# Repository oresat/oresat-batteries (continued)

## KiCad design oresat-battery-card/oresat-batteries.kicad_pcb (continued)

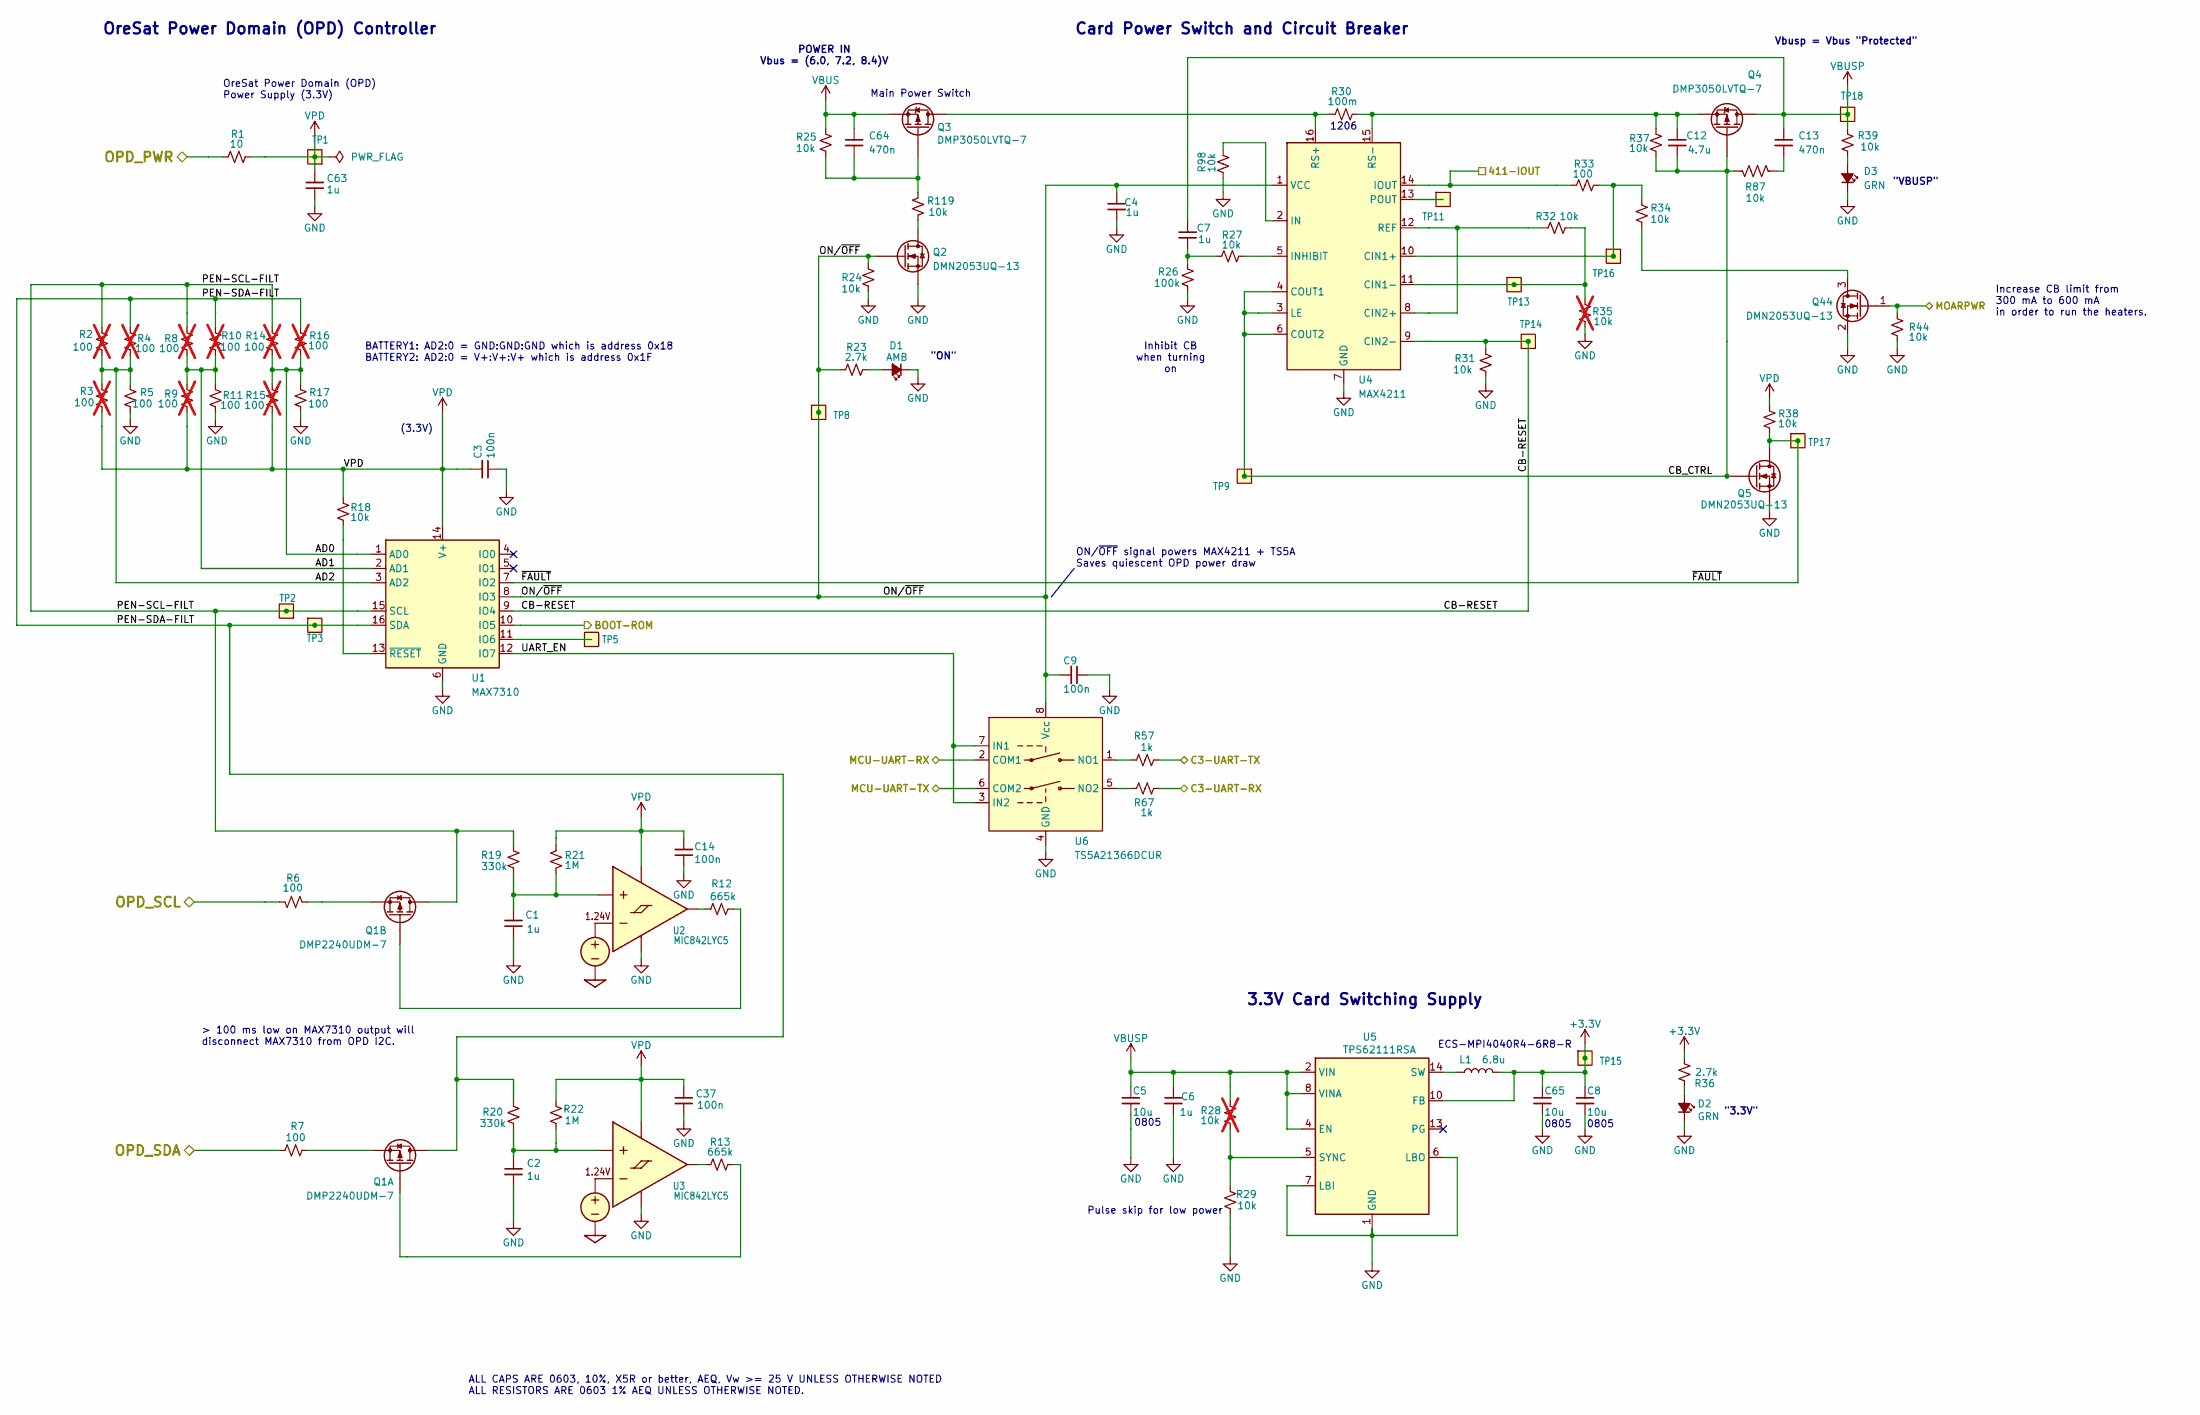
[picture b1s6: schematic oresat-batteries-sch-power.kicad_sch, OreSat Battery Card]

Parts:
C1, C2, C4, C6, C7, C63: 1u; 0603-C-NOSILK; MPN GRT188R71E105KE13D
C3, C9, C14, C37: 100n; 0603-C-NOSILK; MPN C0603C104K5RACAUTO
C5, C8, C65: 10u; 0805-C-NOSILK; MPN GRT21BC71E106KE13K
C12: 4.7u; 0805-C-NOSILK; MPN GRT21BC71E475KE13L
C13, C64: 470n; 0603-C-NOSILK; MPN C0603C474K3RACAUTO
D1: AMB; LED_0603_1608Metric; MPN 150060AS75000
D2, D3: GRN; LED_0603_1608Metric; MPN 150060GS75000
L1: 6.8u; L_ECS-MPI4040; MPN ECS-MPI4040R4-6R8-R
Q1: DMP2240UDM-7; SOT-23-6; MPN DMP2240UDM-7
Q2, Q5, Q44: DMN2053UQ-13; SOT-23; MPN DMN2053UQ-13
Q3, Q4: DMP3050LVTQ-7; TSOT-23-6; MPN DMP3050LVTQ-7
R1: 10; 0603-C-NOSILK; MPN RMCF0603FT10R0
R2, R3, R4, R8, R9, R10, R14, R15, R16: 100; 0603-C-NOSILK; MPN RMCF0603FT100R; not fitted
R5, R6, R7, R11, R17, R33: 100; 0603-C-NOSILK; MPN RMCF0603FT100R
R12, R13: 665k; 0603-C-NOSILK; MPN RMCF0603FT665K
R18, R24, R25, R27, R29, R31, R32, R34, R37, R38, R39, R44, R87, R98, R119: 10k; 0603-C-NOSILK; MPN RMCF0603FT10K0
R19, R20: 330k; 0603-C-NOSILK; MPN RMCF0603FT330K
R21, R22: 1M; 0603-C-NOSILK; MPN RMCF0603FT1M00
R23, R36: 2.7k; 0603-C-NOSILK; MPN RMCF0603FT2K70
R26: 100k; 0603-C-NOSILK; MPN RMCF0603FT100K
R28: 10k; 0603-C-NOSILK; MPN RC0603FR-0710KL; not fitted
R30: 100m; 1206-C; MPN CSR1206FKR100
R35: 10k; 0603-C-NOSILK; MPN RC1005F6653CS; not fitted
R57, R67: 1k; 0603-C-NOSILK; MPN RMCF0603FT1K00
TP1, TP2, TP3, TP5, TP8, TP9, TP11, TP13, TP14, TP15, TP16, TP17, TP18: TEST-POINT-LARGE-SQUARE; TestPoint-0.75mm-th
U1: MAX7310; QFN-16-1EP_4x4mm_P0.65mm_EP2.1x2.1mm; MPN MAX7310ATE+
U2, U3: MIC842LYC5; SOT-353_SC-70-5; MPN MIC842LYC5-TR
U4: MAX4211; QFN-16-1EP_4x4mm_P0.65mm_EP2.1x2.1mm; MPN MAX4211FETE
U5: TPS62111RSA; Texas_RSA_VQFN-16-1EP_4x4mm_P0.65mm_EP2.7x2.7mm; MPN TPS62111RSA
U6: TS5A21366DCUR; VSSOP-8_2.3x2mm_P0.5mm; MPN TS5A21366DCUR

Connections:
+3.3V: C8.1, C65.1, L1.2, R36.2, TP15.1 (1_1), U5.10 (FB); also elsewhere on the board
/C3-UART-RX: R67.2; also elsewhere on the board
/C3-UART-TX: R57.2; also elsewhere on the board
/Microcontroller/411-IOUT: R33.2, U4.14 (IOUT); also elsewhere on the board
/Microcontroller/BOOT-ROM: U1.10 (IO5); also elsewhere on the board
/Microcontroller/MCU-UART-RX: U6.2 (COM1); also elsewhere on the board
/Microcontroller/MCU-UART-TX: U6.6 (COM2); also elsewhere on the board
/Microcontroller/MOARPWR: Q44.1 (G), R44.2; also elsewhere on the board
/OPD_PWR: R1.1; also elsewhere on the board
/OPD_SCL: R6.1; also elsewhere on the board
/OPD_SDA: R7.1; also elsewhere on the board
/OreSat Power Domain (OPD)/AD0: R14.2, R15.1, R16.1, R17.2, U1.1 (AD0)
/OreSat Power Domain (OPD)/AD1: R8.2, R9.1, R10.1, R11.2, U1.2 (AD1)
/OreSat Power Domain (OPD)/AD2: R2.2, R3.2, R4.1, R5.2, U1.3 (AD2)
/OreSat Power Domain (OPD)/CB-RESET: R31.2, TP14.1 (1_1), U1.9 (IO4), U4.9 (CIN2-)
/OreSat Power Domain (OPD)/CB_CTRL: C12.2, Q4.3 (G), Q5.1 (G), R37.1, R87.2, TP9.1 (1_1), U4.3 (LE), U4.4 (COUT1), U4.6 (COUT2)
/OreSat Power Domain (OPD)/ON/~OFF: C4.1, C9.2, Q2.1 (G), R23.2, R24.2, TP8.1 (1_1), U1.8 (IO3), U4.1 (VCC), U6.8 (Vcc)
/OreSat Power Domain (OPD)/PEN-SCL-FILT: Q1.4 (D), R2.1, R8.1, R14.1, R19.2, TP2.1 (1_1), U1.15 (SCL)
/OreSat Power Domain (OPD)/PEN-SDA-FILT: Q1.6 (D), R4.2, R10.2, R16.2, R20.2, TP3.1 (1_1), U1.16 (SDA)
/OreSat Power Domain (OPD)/UART_EN: U1.12 (IO7), U6.3 (IN2), U6.7 (IN1)
/OreSat Power Domain (OPD)/~FAULT: Q5.3 (D), R38.1, TP17.1 (1_1), U1.7 (IO2)
GND: C1.2, C2.2, C3.1, C4.2, C5.2, C6.2, C8.2, C9.1, C14.1, C37.2, C63.2, C65.2, D1.1 (K), D2.1 (K), D3.1 (K), Q2.2 (S), Q5.2 (S), Q44.2 (S), R5.1, R11.1, R17.1, R24.1, R26.1, R29.1, R31.1, R35.1, R44.1, R98.2, U1.6 (GND), U1.17 (GND), U2.2 (GND), U3.2 (GND), U4.7 (GND), U4.17 (GND), U5.1 (GND), U5.6 (LBO), U5.7 (LBI), U5.9 (GND), U5.11 (GND), U5.12 (GND), U5.16 (GND), U5.17 (GND), U6.4 (GND); also elsewhere on the board
unnamed: C7.1, R26.2, R27.2
unnamed: C13.2, R87.1
unnamed: D1.2 (A), R23.1
unnamed: D2.2 (A), R36.1
unnamed: D3.2 (A), R39.1
unnamed: L1.1, U5.14 (SW), U5.15 (SW)
unnamed: Q1.1 (G), R13.2
unnamed: Q1.5 (S), R7.2
unnamed: Q1.3 (G), R12.2
unnamed: Q1.2 (S), R6.2
unnamed: Q2.3 (D), R119.1
unnamed: C64.2, Q3.3 (G), R25.1, R119.2
unnamed: C12.1, Q4.4 (S), R30.2, R37.2, U4.15 (RS-)
unnamed: Q44.3 (D), R34.1
unnamed: TP5.1 (1_1), U1.11 (IO6)
unnamed: R18.1, U1.13 (~RESET)
unnamed: C1.1, R19.1, R21.2, U2.1 (INP)
unnamed: R12.1, U2.4 (OUT)
unnamed: C2.1, R20.1, R22.1, U3.1 (INP)
unnamed: R13.1, U3.4 (OUT)
unnamed: R33.1, R34.2, TP16.1 (1_1), U4.10 (CIN1+)
unnamed: R32.1, R35.2, TP13.1 (1_1), U4.11 (CIN1-)
unnamed: R32.2, U4.8 (CIN2+), U4.12 (REF)
unnamed: R98.1, U4.2 (IN)
unnamed: R27.1, U4.5 (INHIBIT)
unnamed: TP11.1 (1_1), U4.13 (POUT)
unnamed: Q3.1 (D), Q3.2 (D), Q3.5 (D), Q3.6 (D), R30.1, U4.16 (RS+)
unnamed: R28.1, R29.2, U5.5 (SYNC)
unnamed: R57.1, U6.1 (NO1)
unnamed: R67.1, U6.5 (NO2)
VBUS: C64.1, Q3.4 (S), R25.2; also elsewhere on the board
VBUSP: C5.1, C6.1, C7.2, C13.1, Q4.1 (D), Q4.2 (D), Q4.5 (D), Q4.6 (D), R28.2, R39.2, TP18.1 (1_1), U5.2 (VIN), U5.3 (VIN), U5.4 (EN), U5.8 (VINA); also elsewhere on the board
VPD: C3.2, C14.2, C37.1, C63.1, R1.2, R3.1, R9.2, R15.2, R18.2, R21.1, R22.2, R38.2, TP1.1 (1_1), U1.14 (V+), U2.5 (VDD), U3.5 (VDD)

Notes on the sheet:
Card Power Switch and Circuit Breaker
"3.3V"
0805
3.3V Card Switching Supply
(3.3V)
Main Power Switch
"ON"
OreSat Power Domain (OPD) Power Supply (3.3V)
Increase CB limit from 300 mA to 600 mA in order to run the heaters.
Pulse skip for low power
ALL CAPS ARE 0603, 10%, X5R or better, AEQ, Vw >= 25 V UNLESS OTHERWISE NOTED ALL RESISTORS ARE 0603 1% AEQ UNLESS OTHERWISE NOTED.
> 100 ms low on MAX7310 output will disconnect MAX7310 from OPD I2C.
ECS-MPI4040R4-6R8-R
Inhibit CB when turning on
BATTERY1: AD2:0 = GND:GND:GND which is address 0x18 BATTERY2: AD2:0 = V+:V+:V+ which is address 0x1F
POWER IN Vbus = (6.0, 7.2, 8.4)V
Vbusp = Vbus "Protected"
OreSat Power Domain (OPD) Controller
1206
"VBUSP"
ON/~{OFF} signal powers MAX4211 + TS5A Saves quiescent OPD power draw

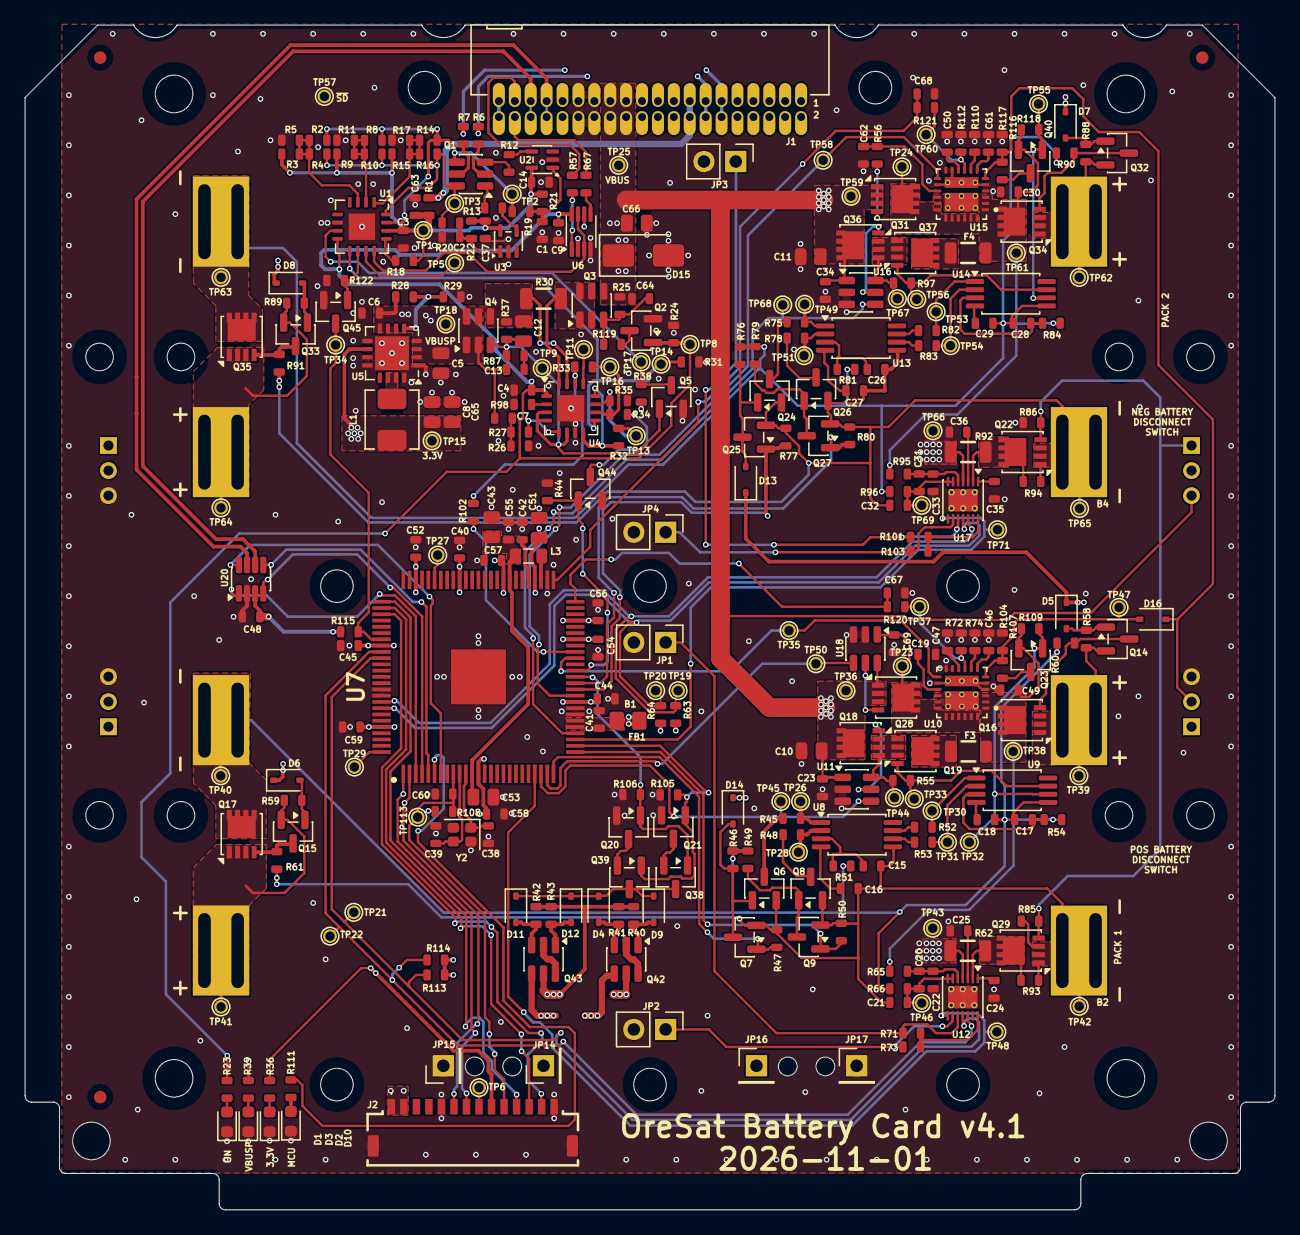
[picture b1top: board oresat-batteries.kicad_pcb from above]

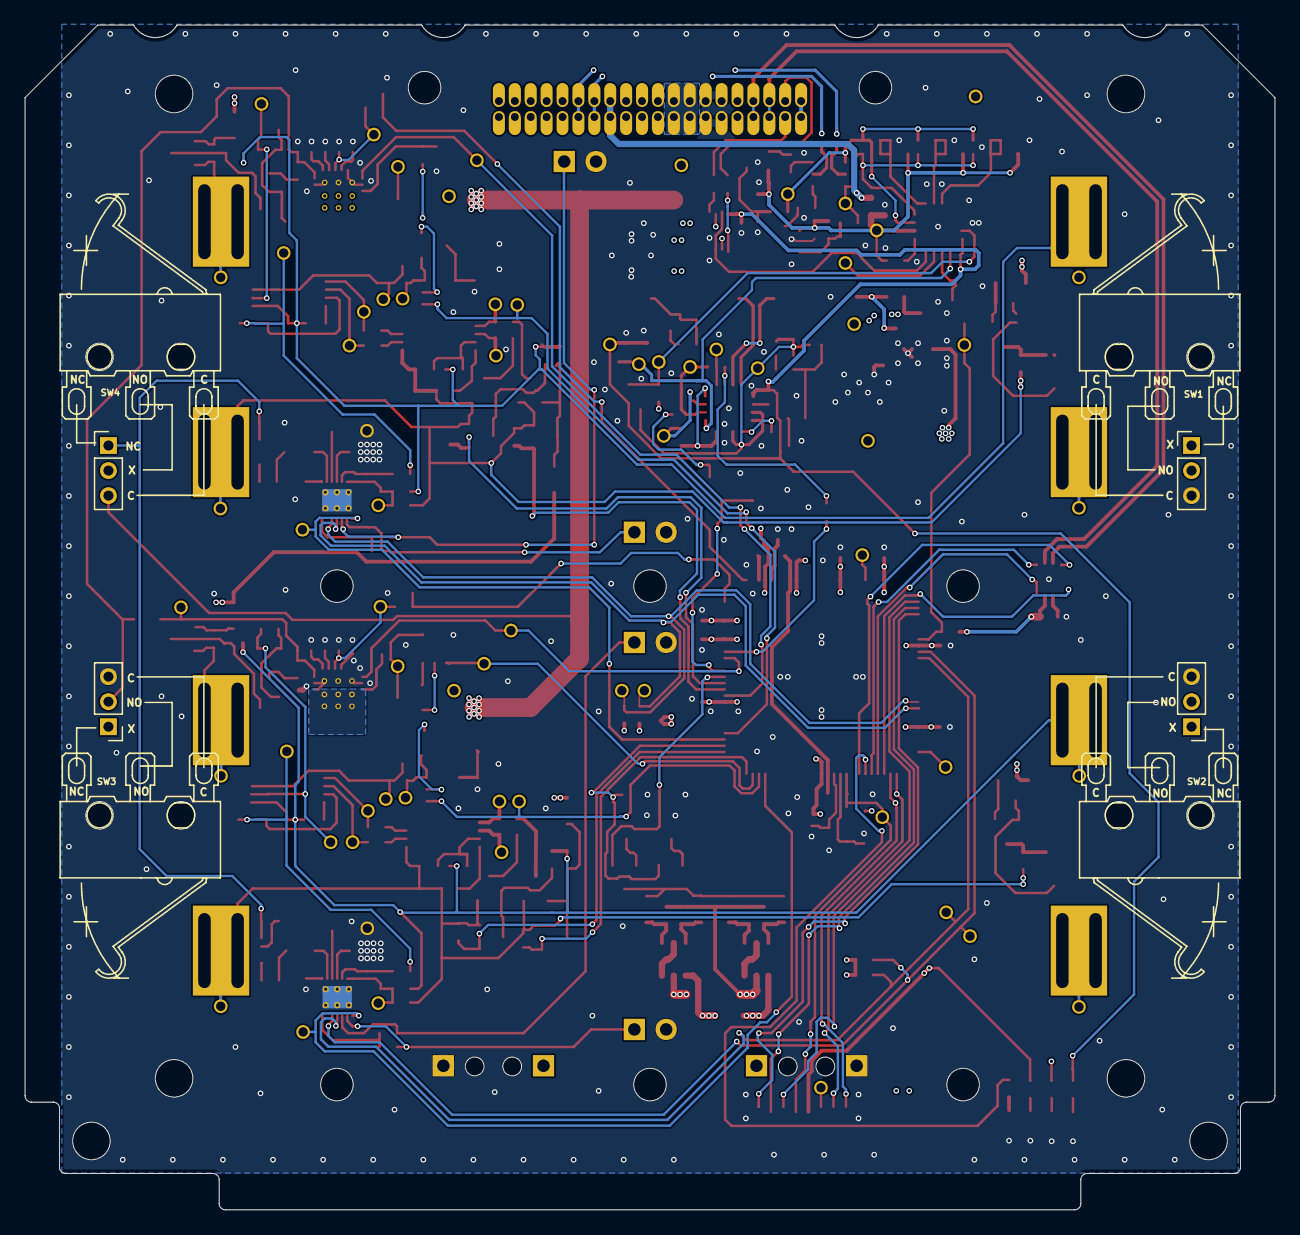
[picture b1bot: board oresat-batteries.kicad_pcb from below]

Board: 4 copper layers, 99.8 x 94.6 mm, 354 parts (4 on the bottom side), 199 nets.

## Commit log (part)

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2016-09-27 Added link to design docs
2016-09-27 Changed link to public view-only.
2017-04-13 Overdue Dump, Added files, libs etc.
2017-04-13 Added crystal, CAN transciever
2017-04-13 Added Parts Selection md
2017-04-14 Changed board to real max dimensions. Added 40pin connector
2017-04-14 Removed locks!
2017-04-14 Added 40 pin for real this time.
2017-04-17 Added block diagram
2017-04-18 Swapped fuel gauge for ti BQ27500
2017-04-25 Replaced BQ27500 with STC300lST
2017-04-26 Added potential battery to schematic
2017-05-04 Started rough layout of boards. Updated design docs (see google docs)
2017-05-06 Finished first draft of schematics.
2017-06-21 Minor clean up, added debug board, serial marker
2017-06-23 Added, resistive heater, half of shutdown circuitry, connected DIG_IOx and SYS_EN pins.
2017-06-23 Fixed Shutdown Circuit, Added more ground pins, cleaned up schematic
2017-06-23 Added TP and nominal V for shutoff
2017-06-23 Named missing NETS
2017-06-23 Replaced Shutdown with new circuitry that will actually work... maybe.
2017-06-24 Cleaned up schematic
2017-06-24 Removed unecessary files and directories.
2017-06-30 Cleaned up schematic, moved STC sense resistor to proper place.
2017-06-30 Schematic Cleanup, added labels and isolated chips visually
2017-06-30 Cleaned up schematci, added frame.
2017-07-01 More cleaning.
2017-07-07 Fixed V- pin on STC
2017-07-07 Fixed TP non-connect issue
2017-07-07 Added ignore for locks. Cleaned up schematic.
2017-07-07 Cleaned up schematic, added filter comp values
2017-07-07 Added comp values
2017-07-08 Cleaned schematic
2017-07-08 First battery board design review. Updated ADP symbol, package, and schematic.
2017-07-11 Cleaned up schematic, reverted to previous configuration for ADP
2017-07-12 Added 3.3V switching power supply
2017-08-16 Added v1.1 to batteries, updated inverter choices in docs.
2017-09-15 Added ideal diodes and new fuel gauge
2017-09-20 Updated batteries with latest OreSat card and connector.
2017-09-23 Added 4412 and toshiba P-Channel Mosfets.
2017-09-23 Added charge and discharge control, lowside shutdown, test points and finished rough v1.1 design.
2017-09-27 Added double pin header.
2017-09-28 Fixed most of the issues from design review Sept 25.
2017-09-28 Cosmetics.
2017-09-28 Cosmetics again.
2017-09-28 Cosmeticas.
2017-10-30 Updates after design review with Austin. Still some TODOs before layout.
2017-11-11 Preliminary layout.
2017-11-17 Cosmetics and polygons.
2017-11-18 Moved to OSH Park 4 layer DRU, fixed some bad/useless layers.
2017-12-04 Cosmetics, moved signals to top and bottom layer.
2017-12-10 Cosmetics, moved all power and signals from gnd layer
2017-12-10 Cleaning, removing airwires.
2018-02-12 Add Gitter badge
2018-03-15 First cleanup of batteries post-Austin going to NASA. Austiiiiinnnnnnnnn, come backgit diff ../design.mdn111git diff ../design.mdn./run More sane two sheet layout on schematic, cleaned up in and out 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
2018-09-24 Fixed body diode issue on output. Changed N to P mosfett for 'trace heater.'
2018-10-04 Assigned IO pins to circuit functions. Finished controls for heater.
2019-03-23 Last changes to previous 1 cell battery pack. Abandoning for 2 cell packs because we're weenies.
2019-03-23 New 2S2P battery boards, based on 18650 cells along with a BQ28400 battery IC.
2019-07-21 removed obsolete documentation
2019-07-21 removed accidental file
2019-07-29 update schematic with s8209 and MAX17205 chips for battery protection and control
2019-07-29 Design review of schematic. Added labels, nets to M0, shutdown circuitry, discussed power domains.
2019-08-02 Eagle updates for battery card 2.0
2019-08-02 handing over to andrew for design review, still needs newest MCAD dxf for inhibit switches
2019-08-06 Updated battery board to latest outline (via oresat-cards.lbr), fixed ground planes, fixed main connector, done for now.
2019-08-06 started revising battery board documenation
2019-08-12 added state diagram, more datasheets, starting moving from 2S2P to 2S1P packs
2019-08-15 version 2.0 of battery card, moved to 2S1P packs, extra battery charge and fuel gauge circuitry, moved to 4 layer board
2019-08-15 png of state diagram
2019-08-15 documentation on S8209 charge protection circuit
2019-08-20 "auto-generated from update_repos.py"
2019-08-24 documentation for the fuel gauge
2019-12-29 New battery schematic and board. New Ablic and SD topology, with battery disconnect circuitry. Updated to Microcontroller and OPD v3.4.
2020-01-13 One 2S1P pack prototype, to be used with a protocard!
2020-01-13 v1.0 of the battery pack prototype board
2020-01-13 Last minute polish on the board.
2020-01-14 Finalized battery prototype, choose parts, made BOM, ordered!
2020-04-16 Latest OreSat battery board form factor, working with Oleg. Now with less tabs, and more slots, and more room
2020-04-17 Latest battery holder DXF with more simple layout and more thermal resistance to frame. Updated battery circuitry from try #3 of the battery prototype. Only one pack layed out, checking in anyway.
2020-04-18 Battery board v1 schematic and layout complete. Lots of checking and polishing left to do, but OMG, finally.
2020-04-18 Now with 100% realistic SOT23-3 transistors and more cleanup.
2020-04-18 More cleanup; added more space in battery tab stitching, and made them hopefully more sane?
2020-04-18 Renumbered parts using built-in renumber tool.
2020-07-12 First real thoughts on inhibit switches.
2020-07-28 Updated battery card with Oleg's drawings; about to upgrade processors.
2020-07-29 New F091 processor. Battery layout done! Still needs polishing.
2020-08-03 Some feedback from design review; more text, 100k instead of 10k for some transistors, still missing heaters.
2020-08-16 Temporary check in; still need to complete heater circuits.
2020-08-17 Updated README, killed design documents. Also, finished layout. Still need to polish, but heater is layed out and doesn't seem to be terrible.
2020-08-17 Polished battery board.
2020-08-17 More documentation cleanup
2020-08-17 Oh, uh, yeah, include the CERN OHL
2020-08-17 remove old prototype files
2020-08-25 Added tolerance note to heaters.
2020-08-29 fixed a couple left over attributes and formatted BOM
2020-09-14 Made sure all files are tracked in git.
2020-12-29 Added PDF of block diagram
2020-12-29 Removed weird file
2020-12-29 Added weird file to .gitignore.
2021-03-01 OreSat Battery Card v2.0
    Changes based on finally fixing the C3 watchdog timer and the interactions between the two.
    - Moved right hand ground cut switch to vbat switch. This solves a *lot* of problems with removing the ground and shutdown not working correctly.
    - Got rid of "fast charge" and split the charge / discharge paths with independent PTC (5A out, 2A in).
    - Switched most everytthing to 100k. 1M wasn't enough to overcome leakage, and 10k was too much.
    - Fixed the ablic bypass cap which should have gone right to VDD.
    - Rerouted !SD for lots of paranoia.
2021-03-01 Full update of the BOM; added non PCB materials including the heaters, thermistors. Updated fuses to be decent PTCs. Might regret that later, but it really seems like the right thing.
2021-03-17 Upped battery board to v2.1. No real changes, besides adding fiducials (blargh!), updating the board version, and adding the flight marker to TPLACE.
    More importantly, the BOM has been upadated to reflect what Screaming Circuits is going to stuff for us.
2021-03-27 Updated shutdown mosfet resistors to 100k after the battery failed quiescent power draw, and removed backup thermistors from the BOM.
2021-04-09 OreSat Battery Card v2.1
    - Shrunk fastener foot prints to gain more room.
    - Redid DF3 switch layouts to get the jumper wires closer to the switche's mini-contact holes.
    - Added fiducials.
    - Replaced quad N channel MOSFET with four N channels because the quad pack is unobtainium right now.
2021-04-20 Fixed off by one on BOM
2021-10-07 Update README.md
    Link to google doc
2021-11-09 Battery v3.0. Might actually work, and with less dropouts.
2021-11-09 v3.0 sent off to fab! Updated BOM, and committed final changes to card. Lots of small changes, including better power routing, resistors in the UART line to the C3, and as mentioned in an earlier com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
2021-12-29 Added inhibit block diagram schematic and PDF.
2022-01-28 Updated inhibit switch diagram to be more compact, reflect Nanoracks SDT call outs
2022-07-13 Migrated to KiCad
2022-07-28 Fixed a ton of DRC errors, maybe found some problems
2022-07-28 The DRC is happy now
2022-07-29 Fixed the voltage regulator problem, and the DRC is happy
2023-06-18 Updated kicad import of battery card v3.0
2023-12-02 Updating KiCAD import of EAGLE battery card v3.0 and calling it v3.1 because the gerber files will definitely be different and we'll probably implement a few small changes. Reimports, renames, and fi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
2023-12-02 Updated readme and picture.
2023-12-02 Minor fix to README
2023-12-02 Maybe it's better if there's not an extra copy of the KiCAD import files?
2023-12-02 Kicad import try #3. Now with DXFs from custom EAGLE layers. Schematic worksheets and names updated.
2023-12-02 Move main connector to kicad libraries; start updating text size.
2023-12-02 Transferred connector page to oresat-kicad. Added correct card outline.
2023-12-03 Updated ground planes, battery foot prints, zones needs more work.
2023-12-03 better schematic layout (no netlist changes) on battery packs, and updated DRUs and fixed some minor DRU issues.
2024-01-04 Adding MLI template v1.0
2024-01-04 Expanded a few mm to catch more battery area
2024-01-04 Add some external dimensions
2024-01-05 README now links to PCBA and assembly BOMs.
2024-01-05 Update README.md
    Link to OnShape
2025-12-27 Added NASA ISS Safety Committee approved inhibits block diagram
2026-01-11 Starting Battery Card 4.0
    Changed root sheet to hierarchical sheet. No change to schematic or layout yet. Updated the stackup with oresat template. Switched to variables for version and date.
2026-01-11 Minor polishing, removing outdated OPD signals and OPD power jumper.
2026-01-11 Added +battery disconect mosfet and switch
2026-01-11 Negative battery disconnects in. Ready for KiCad component upgrade.
2026-01-14 Renovated Schematic
    Updated schematic symbols and made more uniform with changed resistor, capacitor, and FET symbols. Changed 0603 cap foot print to 0603 small in Oresat passives. Added 2 new resistors and 2 new caps i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
2026-02-01 Progress on v4
    Figure out to bypass negative battery cutoff with 10k to make sure that nSHUTDOWN always works. Lots of moving around (it's tight), finally got pack 1 done. Working on the Pack 2.
2026-02-02 Progress on battery card v4
    Moved in -batt cutoffs, which caused a lot of pain and suffering. Started updating BOM, and fixed all transistor packages. Updated resistor packages, too. Still needs a lot of cleanup, but probably 8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
2026-02-03 Routing complete!
2026-02-03 Updated BOM, ready for polish and switch to MCXN
2026-03-12 Test out shallow clone
    Git demonstration
2026-03-23 Not sure what changed from back in February, but committing anyway :)
2026-03-23 Updated data, spiffed up the root page, renamed some STM specific OPD signals, synced SCH and BRD, fixed a bunch of DRC errors, NOW ready for MCXN import that will screw everything up.
2026-03-23 Added MCXN. Preliminary power layout, started removal of old symbols and footprints.
2026-04-05 Routed unconnected lines - needs DRC fixes and review
2026-04-05 Cleaned Up DRC errors & silkscreen
    Should be good? Needs review. Only 2 warnings left, "isolated copper fill" for zones Q36-D etc...
2026-05-14 Updated gitignore file for KiCad 10
2026-05-14 Revision 2.1 of the OreSat1 battery inhibits block diagram. Committing PDF for posterity
2026-05-14 Intermediary state on v4. Added one of two efuses.
2026-06-05 Schematic complete with new TPS circuit breaker; layout in progress
